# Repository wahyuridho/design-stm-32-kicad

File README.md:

# design-stm-32-kicad
Ini merupakan design dari stm32 yang saya buat menggunakan software Kicad. silahkan apabila anda ingin menggunakan design yang saya buat bisa lakukan modifikasi 
sesuai keinginan anda. 

note : silahkan cek tampilan 3D pada kicad untuk memastikan bahwa design yang dibuat sudah benar

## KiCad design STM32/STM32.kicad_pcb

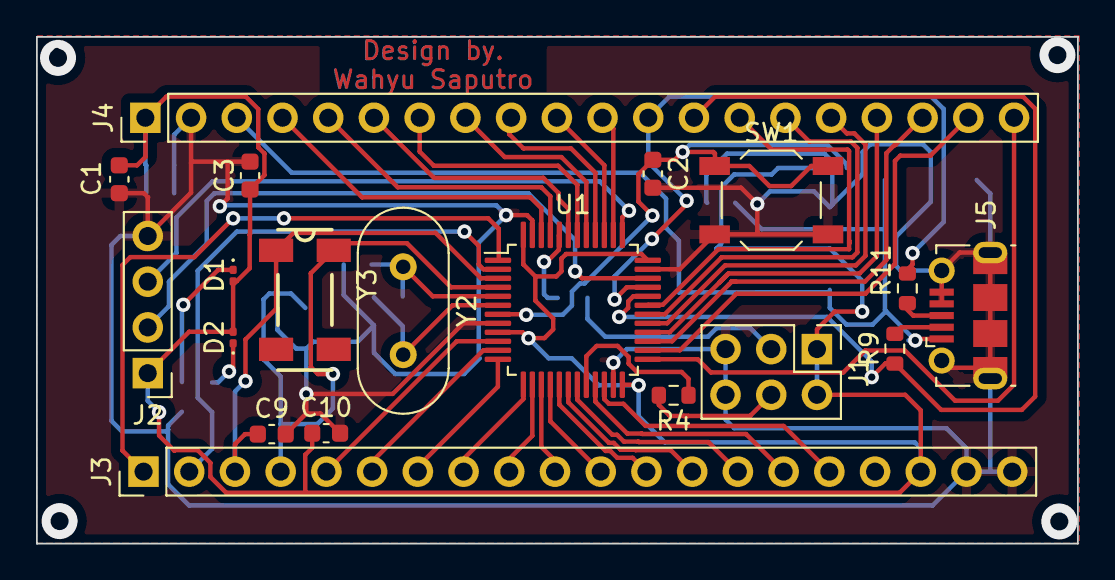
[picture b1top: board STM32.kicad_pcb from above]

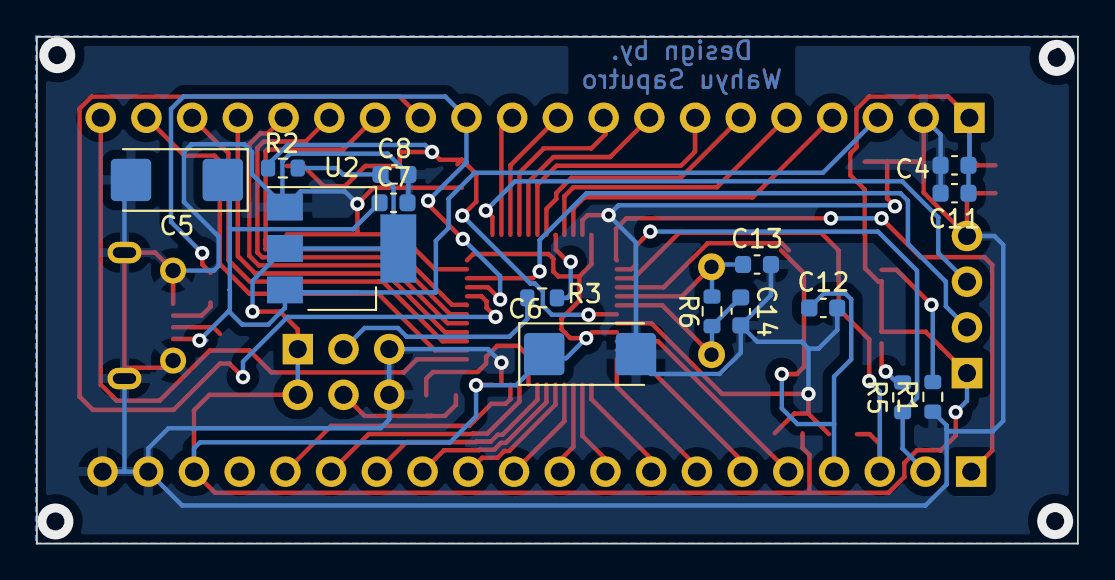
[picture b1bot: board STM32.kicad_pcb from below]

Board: 2 copper layers, 57.8 x 28.2 mm, 34 parts (15 on the bottom side), 49 nets.

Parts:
C1, C3, C4, C10, C11: 104,0603; C_0603_1608Metric
C2: 105,0603; C_0603_1608Metric
C5: 100uF; CP_EIA-6032-15_Kemet-U_Pad2.25x2.35mm_HandSolder
C6: 330uF; CP_EIA-6032-15_Kemet-U_Pad2.25x2.35mm_HandSolder
C7, C8: 100nF,0603; C_0603_1608Metric
C9, C12, C13, C14: 20p,0603; C_0603_1608Metric
D1, D2: LED; LED_0201_0603Metric
J1: Header 3x2; PinHeader_2x03_P2.54mm_Vertical
J2: SWD; PinHeader_1x04_P2.54mm_Vertical
J3, J4: Header 20; PinHeader_1x20_P2.54mm_Vertical
J5: USB_B_Micro; USB_Micro-B_Molex-105017-0001
R1, R5: 510R,0603; R_0603_1608Metric
R2: 10k,0603; R_0603_1608Metric
R3, R4: 100k,0603; R_0603_1608Metric
R6: 1M; R_0603_1608Metric
R9, R11: 200R,0603; R_0603_1608Metric
SW1: SW_Push; SW_SPST_TL3342
U1: STM32F103C8Tx; LQFP-48_7x7mm_P0.5mm
U2: AMS1117-3.3; SOT-223-3_TabPin2
Y2: 8MHz; Crystal_HC49-4H_Vertical
Y3: 32.768K; MC-306

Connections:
/5V: C5.1, C7.1, J4.3, J5.1 (VBUS), U2.3 (VI)
/BOOT0: R3.2, U1.44 (BOOT0)
/OSCIN: C13.1, R6.1, U1.5 (PD0), Y2.1
/OSCOUT: C14.1, R6.2, U1.6 (PD1), Y2.2
/PA0: J3.5, U1.10 (PA0)
/PA1: J3.6, U1.11 (PA1)
/PA2: J3.7, U1.12 (PA2)
/PA3: J3.8, U1.13 (PA3)
/PA4: J3.9, U1.14 (PA4)
/PA5: J3.10, U1.15 (PA5)
/PA6: J3.11, U1.16 (PA6)
/PA7: J3.12, U1.17 (PA7)
/PA8: J4.16, U1.29 (PA8)
/PA9: J4.15, U1.30 (PA9)
/PA10: J4.14, U1.31 (PA10)
/PA11: J4.13, R9.1, U1.32 (PA11)
/PA12: J4.12, R11.1, U1.33 (PA12)
/PA15: J4.11, U1.38 (PA15)
/PB0: J3.13, U1.18 (PB0)
/PB1: J3.14, U1.19 (PB1)
/PB2/BOOT1: R4.1, U1.20 (PB2)
/PB3: J4.10, U1.39 (PB3)
/PB4: J4.9, U1.40 (PB4)
/PB5: J4.8, U1.41 (PB5)
/PB6: J4.7, U1.42 (PB6)
/PB7: J4.6, U1.43 (PB7)
/PB8: J4.5, U1.45 (PB8)
/PB9: J4.4, U1.46 (PB9)
/PB10: J3.15, U1.21 (PB10)
/PB11: J3.16, U1.22 (PB11)
/PB12: J4.20, U1.25 (PB12)
/PB13: J4.19, U1.26 (PB13)
/PB14: J4.18, U1.27 (PB14)
/PB15: J4.17, U1.28 (PB15)
/PC13: J3.2, R5.1, U1.2 (PC13)
/RESET: C2.1, R2.2, SW1.1, U1.7 (NRST)
/SWCLK: J2.3, U1.37 (PA14)
/SWIO: J2.2, U1.34 (PA13)
/VBAT: J3.1, U1.1 (VBAT)
/VCC3V3: C1.1, C3.1, C4.1, C6.1, C8.1, C10.1, C11.1, D1.2 (A), D2.2 (A), J1.1, J1.2, J2.1, J3.18, J4.1, R2.1, U1.9 (VDDA), U1.24 (VDD), U1.36 (VDD), U1.48 (VDD), U2.2 (VO)
GND: C1.2, C2.2, C3.2, C4.2, C5.2, C6.2, C7.2, C8.2, C9.2, C10.2, C11.2, C12.2, C13.2, C14.2, J1.5, J1.6, J2.4, J3.19, J3.20, J4.2, J5.4 (ID), J5.5 (GND), J5.6 (Shield), R1.1, SW1.2, U1.8 (VSSA), U1.23 (VSS), U1.35 (VSS), U1.47 (VSS), U2.1 (GND)
unnamed: D1.1 (K), R1.2
unnamed: D2.1 (K), R5.2
unnamed: J1.3, R3.1
unnamed: J1.4, R4.2
unnamed: J5.2 (D-), R9.2
unnamed: J5.3 (D+), R11.2
PC14: C9.1, J3.3, U1.3 (PC14), Y3.1
PC15: C12.1, J3.4, U1.4 (PC15), Y3.4

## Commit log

2022-02-05 first design
